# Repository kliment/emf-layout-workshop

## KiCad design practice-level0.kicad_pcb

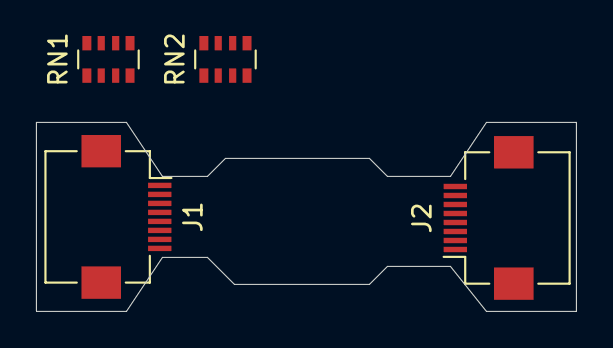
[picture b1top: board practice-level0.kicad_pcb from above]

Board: 2 copper layers, 30.0 x 10.5 mm, 4 parts (0 on the bottom side), 16 nets, no tracks yet.

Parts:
J1, J2: Conn_01x08; Hirose_FH12-8S-0.5SH_1x08-1MP_P0.50mm_Horizontal
RN1, RN2: R_Pack04; R_Array_Convex_4x0603

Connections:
unnamed: J1.1, RN1.1
unnamed: J1.2, RN1.2
unnamed: J1.3, RN1.3
unnamed: J1.4, RN1.4
unnamed: J1.5, RN2.1
unnamed: J1.6, RN2.2
unnamed: J1.7, RN2.3
unnamed: J1.8, RN2.4
unnamed: J2.1, RN2.5
unnamed: J2.2, RN2.6
unnamed: J2.3, RN2.7
unnamed: J2.4, RN2.8
unnamed: J2.5, RN1.5
unnamed: J2.6, RN1.6
unnamed: J2.7, RN1.7
unnamed: J2.8, RN1.8

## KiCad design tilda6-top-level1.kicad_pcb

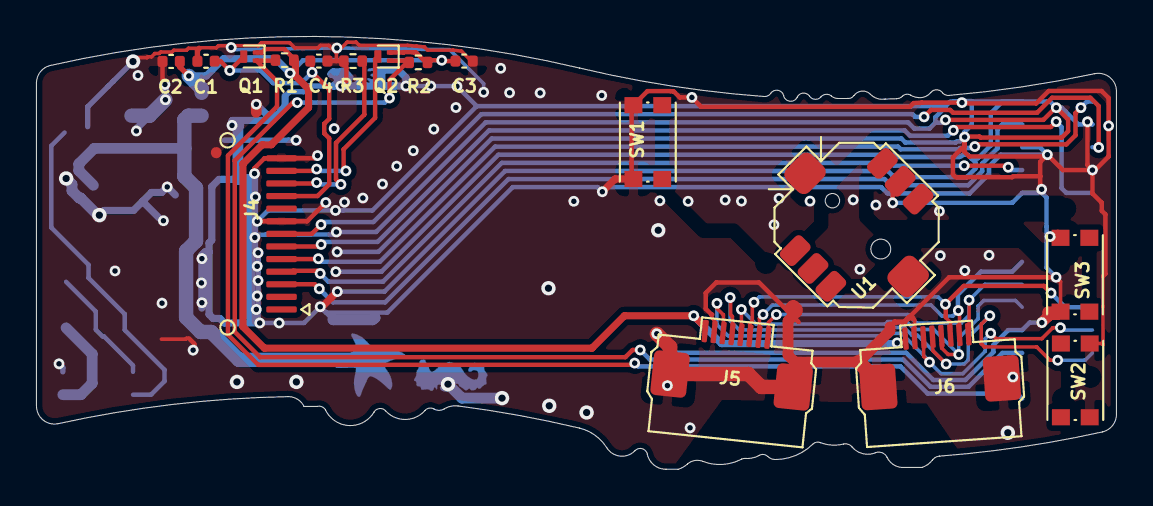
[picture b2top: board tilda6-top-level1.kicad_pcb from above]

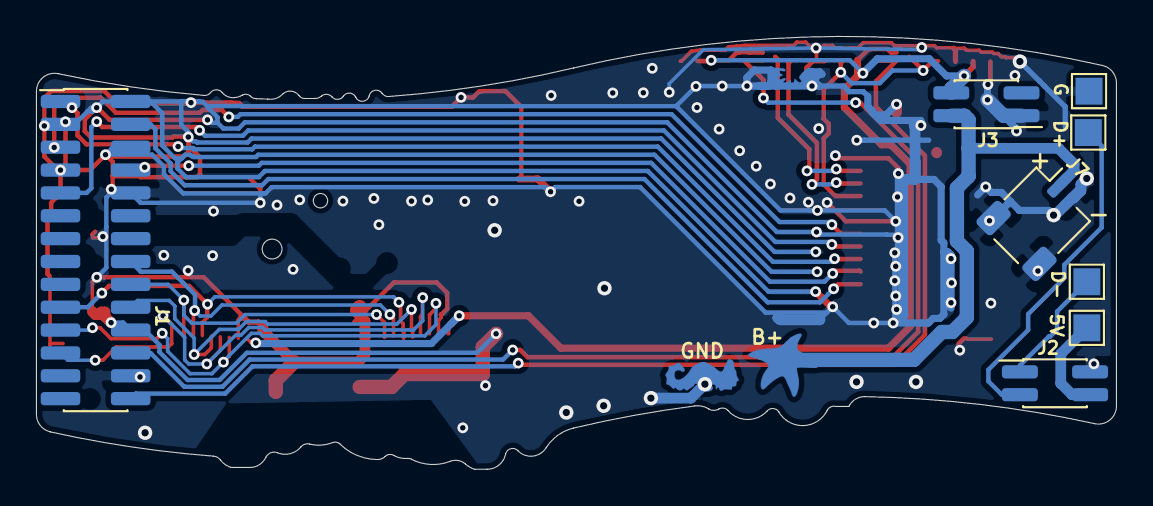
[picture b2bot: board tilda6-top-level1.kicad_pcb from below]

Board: 2 copper layers, 60.0 x 24.0 mm, 26 parts (10 on the bottom side), 30 nets.

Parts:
C1, C2: 1u; C_0402_1005Metric
C3, C4: 10n; C_0402_1005Metric
J1: Conn_02x14_Odd_Even; PinHeader_2x14_P1.27mm_Vertical_SMD
J2, J3: Conn_02x02_Odd_Even; PinHeader_2x02_P1.27mm_Vertical_SMD
J4: Conn_01x13; ER-TFT-1.14
J5, J6: Conn_01x08; XUNPU_FPC-05F-8PH20
J7: Conn_01x02_Female; JST_SH_SM02B-SRSS-TB_1x02-1MP_P1.00mm_Horizontal
Q1, Q2: LP0404N3T5G; SOT-883
R1, R2: 10k; R_0402_1005Metric
R3: 47R; R_0402_1005Metric
SW1, SW2, SW3: SW_Push; SW_Push_1P1T_NO_CK_KMR2
TP1: TestPoint; art-plus-star
TP2: TestPoint; art-minus-horse
TP3, TP4, TP5, TP6: TestPoint; TestPoint_Pad_1.5x1.5mm
U1: 5-WAY-JOYSTICK; JOYSTICK-5-WAY

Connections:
/3V3: C2.1, C3.1, J3.4, J5.1, J6.1, Q1.2, Q2.2, R1.1, R2.1
/BATTERY+: J3.2, J7.1, TP1.1
/BTN3: J1.14, SW1.1
/D+: J2.3, TP3.1
/D-: J2.1, TP5.1
/DISPLAY_3V3: C1.1, C4.1, J4.10, Q1.3
/EN: J1.27, SW2.1
/G0: J1.20, J5.5, J6.5
/G1: J1.19, J5.6, J6.6
/G2: J1.16, J5.7, J6.7
/G3: J1.18, J5.8, J6.8
/I2C_SCL: J1.23, J5.4, J6.4
/I2C_SDA: J1.21, J5.3, J6.3
/IO0: J1.25, SW3.1
/JOYC: J1.12, U1.2
/JOYD: J1.13, U1.6
/JOYL: J1.17, U1.3
/JOYR: J1.15, U1.4
/JOYU: J1.11, U1.1
/LCD_BL_A: J4.12, Q2.3
/LCD_BL_C: J4.11, R3.1
/LCD_BL_EN: J1.24, Q2.1, R2.2
/LCD_CLK: J1.8, J4.4
/LCD_CS: J1.5, J4.7
/LCD_DC: J1.1, J4.5
/LCD_DIN: J1.4, J4.3
/LCD_PWR_EN: J1.28, Q1.1, R1.2
/LCD_RST: J1.9, J4.6
/VBUS: J2.4, TP4.1
GND: C1.2, C2.2, C3.2, C4.2, J1.2, J1.3, J1.6, J1.7, J1.10, J1.22, J1.26, J2.2, J3.1, J4.8, J4.13, J5.2, J6.2, J7.2, R3.2, SW1.2, SW2.2, SW3.2, TP2.1, TP6.1, U1.5

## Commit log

2022-06-04 add practice boards
